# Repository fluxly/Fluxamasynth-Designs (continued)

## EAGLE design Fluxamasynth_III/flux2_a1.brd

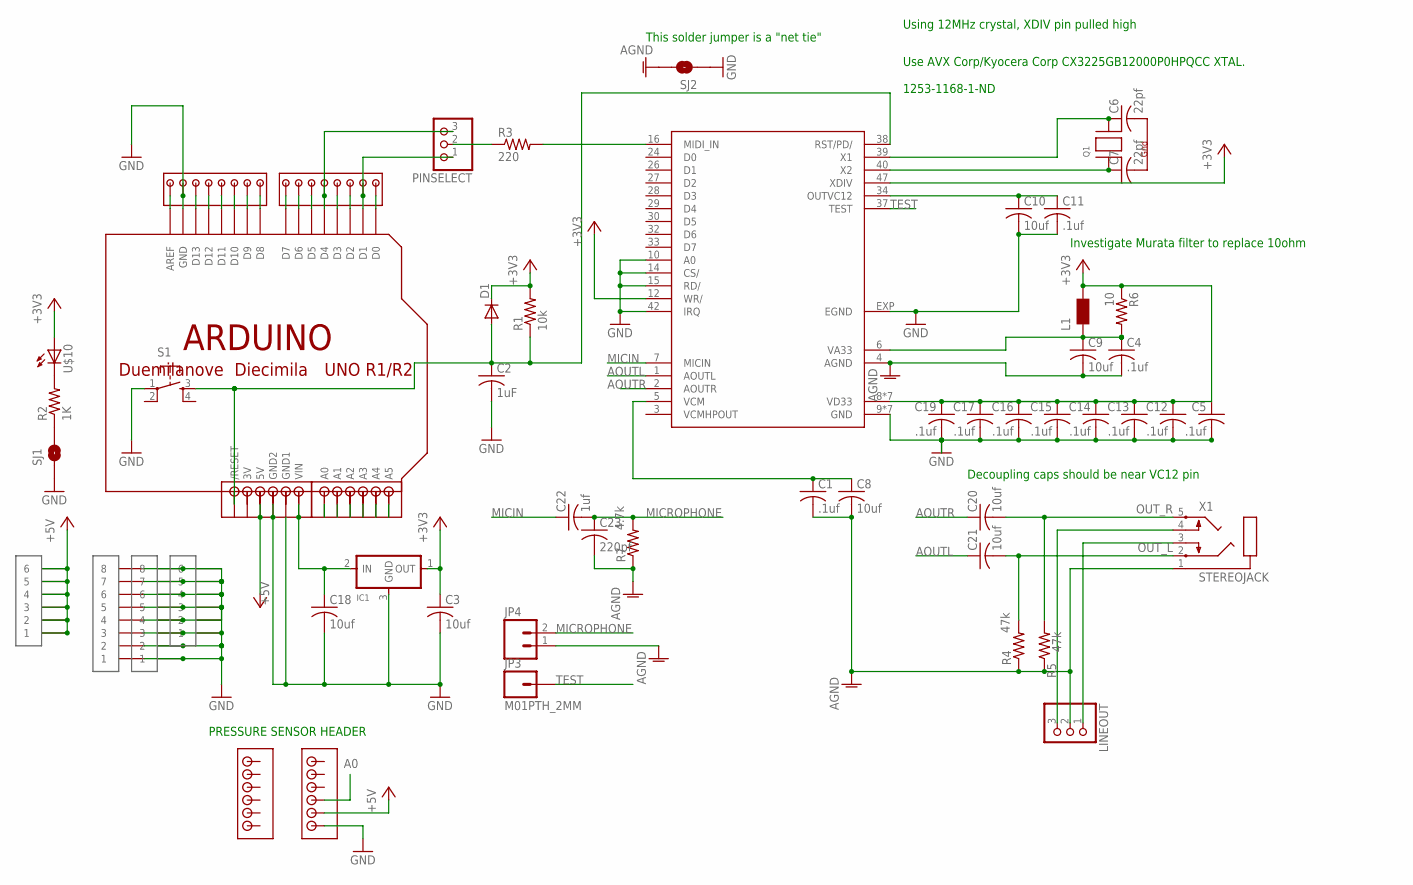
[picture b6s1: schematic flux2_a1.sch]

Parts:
C1, C4, C5, C11, C12, C13, C14, C15, C16, C17, C19: .1uf; C0805
C2: 1uF; C0805
C3, C8, C9, C10, C18, C20, C21: 10uf; C0805
C6, C7: 22pf; C0805
C22: 1uf; C0805
C23: 220pf; C0805
D1: DIODESOD123; SOD123
IC1: REGULATORSOT23; SOT23
JP3: M01PTH_2MM; 1X01_2MM
JP4: M02PTH; 1X02
L1: FERRITE_BEAD_L0603; R0603
LINEOUT: PINHD-1X3; 1X03
PINSELECT: PINHD-1X3; 1X03
Q1: MODERNDEVICE_XTAL-4-3225; MODERNDEVICE_NX3225
R1: 10k; M0805
R2: 1K; M0805
R3: 220; M0805
R4, R5: 47k; M0805
R6: 10; M0805
R7: 4.7k; M0805
S1: 6MM_SWITCH6MM_SWITCH; 6MM_SWITCH
SJ1, SJ2: MODERNDEVICE_SOLDERJUMPERTRACE; MODERNDEVICE_SJ_2S-TRACE
U1: SAM2695; QFN48
U$1, U$11: 1X8_CLEAN
U$2, U$3: 1X6_CLEAN
U$4, U$5, U$7, U$8: 1X6HEADER
U$6, U$9: 1X8HEADER
U$10: LED1206; 1206
U$12: ARDUINO-NOHOLE
X1: STEREOJACK; STX3100

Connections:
3V: U$12.3V
+3V3: C3.1, D1.CATHODE (C), IC1.1 (OUT), L1.2, R1.2, R6.1, U1.12 (WR/), U1.47 (XDIV), U$10.1 (A)
+5V: U$2.P$1 (1), U$2.P$2 (2), U$2.P$3 (3), U$2.P$4 (4), U$2.P$5 (5), U$2.P$6 (6), U$7.P$2, U$8.P$3, U$12.5V
A0: U$5.P$1, U$7.P$3, U$12.A0
AGND: C1.2, C4.2, C8.2, C9.2, C23.2, JP4.1, LINEOUT.2, R4.1, R5.1, R7.1, SJ2.2, U1.4 (AGND), X1.1
AOUTL: C21.1, U1.1 (AOUTL)
AOUTR: C20.1, U1.2 (AOUTR)
GND: C2.2, C3.2, C5.2, C10.2, C11.2, C12.2, C13.2, C14.2, C15.2, C16.2, C17.2, C18.2, C19.2, IC1.3 (GND), S1.1, SJ1.1, SJ2.1, U1.9 (GND), U1.10 (A0), U1.13 (GND), U1.14 (CS/), U1.15 (RD/), U1.18 (GND), U1.25 (GND), U1.36 (GND), U1.42 (IRQ), U1.45 (GND), U1.48 (GND), U1.EXP (EGND), U$1.P$1 (1), U$1.P$2 (2), U$1.P$3 (3), U$1.P$4 (4), U$1.P$5 (5), U$1.P$6 (6), U$1.P$7 (7), U$1.P$8 (8), U$3.P$1 (1), U$3.P$2 (2), U$3.P$3 (3), U$3.P$4 (4), U$3.P$5 (5), U$3.P$6 (6), U$7.P$1, U$8.P$4, U$9.P$2, U$11.P$1 (1), U$11.P$2 (2), U$11.P$3 (3), U$11.P$4 (4), U$11.P$5 (5), U$11.P$6 (6), U$11.P$7 (7), U$11.P$8 (8), U$12.GND, U$12.GND1, U$12.GND2
MICIN: C22.1, U1.7 (MICIN)
MICROPHONE: C22.2, C23.1, JP4.2, R7.2
unnamed: PINSELECT.2, R3.1
unnamed: R3.2, U1.16 (MIDI_IN)
unnamed: C5.1, C12.1, C13.1, C14.1, C15.1, C16.1, C17.1, C19.1, U1.8 (VD33), U1.11 (VD33), U1.20 (VD33), U1.31 (VD33), U1.35 (VD33), U1.41 (VD33), U1.46 (VD33)
unnamed: C10.1, C11.1, U1.34 (OUTVC12)
unnamed: R2.2, U$10.2 (C)
unnamed: C1.1, C8.1, U1.5 (VCM)
unnamed: U$9.P$8, U$12.D8
unnamed: PINSELECT.1, U$6.P$7, U$12.D1
unnamed: PINSELECT.3, U$6.P$4, U$12.D4
unnamed: U$9.P$7, U$12.D9
unnamed: LINEOUT.3, X1.4
unnamed: U$9.P$5, U$12.D11
unnamed: U$9.P$6, U$12.D10
unnamed: LINEOUT.1, X1.3
unnamed: U$9.P$4, U$12.D12
unnamed: U$9.P$3, U$12.D13
unnamed: U$6.P$2, U$12.D6
unnamed: U$9.P$1, U$12.AREF
unnamed: U$6.P$3, U$12.D5
unnamed: U$6.P$8, U$12.D0
unnamed: U$6.P$6, U$12.D2
unnamed: U$6.P$5, U$12.D3
unnamed: U$6.P$1, U$12.D7
unnamed: C2.1, D1.ANODE (A), R1.1, S1.3 (S), U1.38 (RST/PD/), U$8.P$1
unnamed: C4.1, C9.1, L1.1, R6.2, U1.6 (VA33)
unnamed: U$5.P$2, U$12.A1
unnamed: U$5.P$3, U$12.A2
unnamed: U$5.P$4, U$12.A3
unnamed: U$5.P$5, U$12.A4
unnamed: U$5.P$6, U$12.A5
unnamed: R2.1, SJ1.2
unnamed: C6.1, Q1.3 (X2), U1.39 (X1)
unnamed: C7.1, Q1.1 (X1), U1.40 (X2)
unnamed: C6.2, Q1.2 (G2)
unnamed: C7.2, Q1.4 (G1)
OUT_L: C21.2, R4.2, X1.2
OUT_R: C20.2, R5.2, X1.5
TEST: JP3.1, U1.37 (TEST)
VIN: C18.1, IC1.2 (IN), U$8.P$6, U$12.VIN

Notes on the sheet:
PRESSURE SENSOR HEADER
Using 12MHz crystal, XDIV pin pulled high
Investigate Murata filter to replace 10ohm
Use AVX Corp/Kyocera Corp CX3225GB12000P0HPQCC XTAL. 1253-1168-1-ND
Decoupling caps should be near VC12 pin
This solder jumper is a "net tie"

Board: 2 copper layers, 55 parts (0 on the bottom side), 48 nets, no tracks yet.

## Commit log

2018-02-06 first
2018-02-06 add design files
2018-05-23 Feather, Pi updates
